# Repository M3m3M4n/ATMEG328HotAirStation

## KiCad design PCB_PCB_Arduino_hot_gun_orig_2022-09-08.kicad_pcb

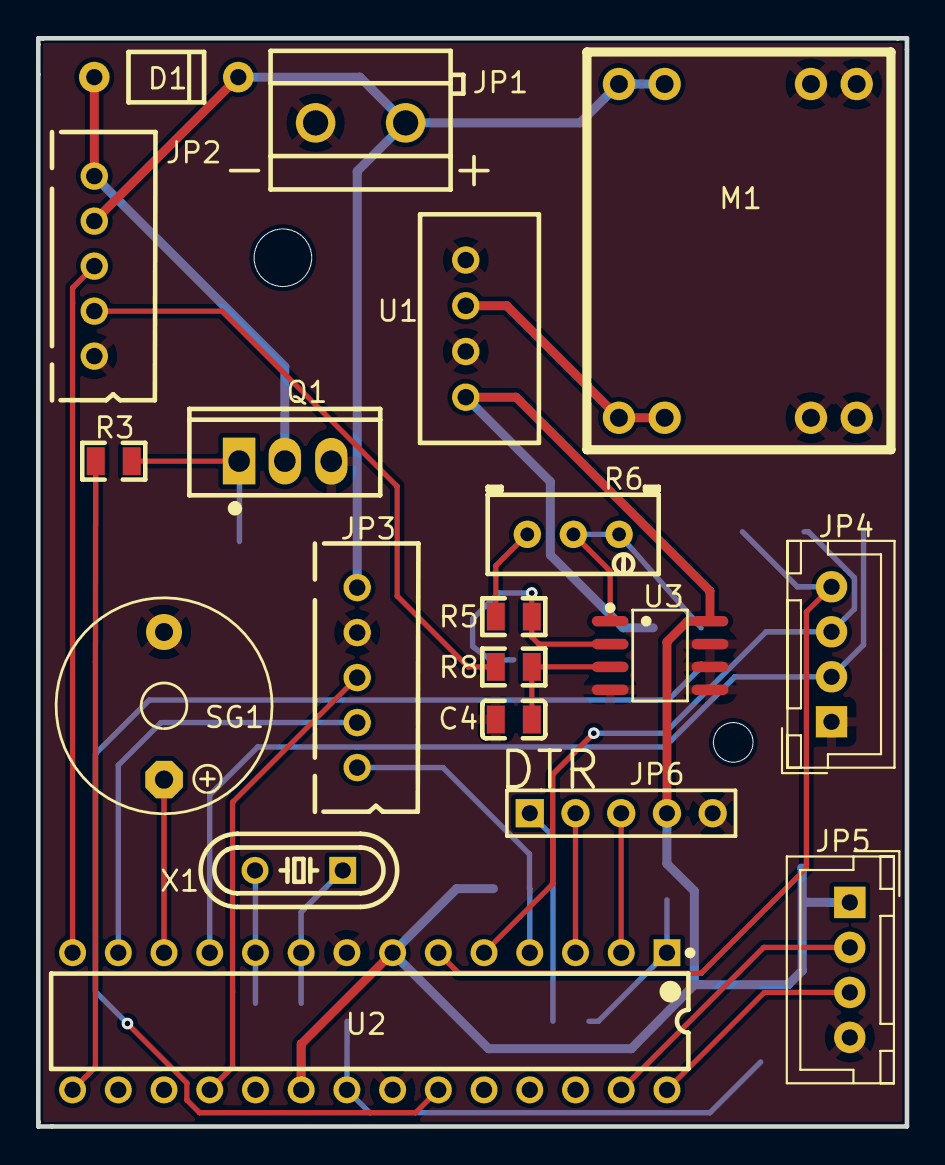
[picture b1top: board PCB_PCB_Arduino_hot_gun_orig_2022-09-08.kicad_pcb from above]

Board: 2 copper layers, 48.3 x 60.5 mm, 34 parts (0 on the bottom side), 30 nets.

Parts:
C1, C2: 22pF; C0805
C3, C4, C5, C6, C7, C8: 100n; C0805
C9, C10: 100u; C0805
D1: FR107; DO-41_BD2.8-L4.2-P8.00-D0.7-FD
JP1: 24v; CONN-TH_P5.00_KF301-5.0-2P
JP2: Air Gun; JST-XH-TH-5-2.5
JP3: INTERFACE; JST-XH-TH-5-2.5
JP4, JP5: REF; JST_XH_B04B-XH-A_04X2.50MM_STRAIGHT
JP6: UART; HDR-M-2.54_1X5
M1: .Designator; MP1584
Q1: IRFZ44NPBF; TO-220-3_L10.0-W4.5-P2.54-L
R1, R2, R5, R8, R11: 10k; R0805
R3: 100; R0805
R6: 500k; RES-ADJ_3296W
R7: 470; R0805
R9: 1k; R0805
SG1: BUZZER
U1: TME 0505S
U2: ATMEGA328P-PU; DIP-28_300MIL
U3: LM358; SOIC-8_L4.9-W3.9-P1.27-LS6.0-BL
U4: 1117-3.3; AMS_1117
X1: 16MHz; HC-49S

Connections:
24V: D1.2, JP1.2, JP2.4, JP3.5, M1.1, M1.2
+5V: C5.2, C9.2, JP5.1, JP6.4, R1.1, R11.1, U1.4, U2.7, U2.20, U3.8, U4.3
AC_RELAY: JP3.3, U2.18
AC_ZERO: JP3.1, R1.2, U2.4
BTN: C8.2, JP4.2, U2.11
D1_1: D1.1, JP2.5, Q1.2
ENC_L: C7.2, JP4.3, U2.5
ENC_R: C6.2, JP4.4, U2.6
FAN_POWER: R3.1, U2.15
GND: C1.2, C2.2, C4.1, C5.1, C6.1, C7.1, C8.1, C9.1, C10.1, JP1.1, JP2.1, JP3.4, JP4.1, JP5.4, JP6.5, M1.3, M1.4, M1.5, M1.6, Q1.3, R2.1, R9.1, U1.1, U1.3, U2.8, U2.22, U3.4, U3.5, U3.6, U3.7, U4.1
GUN_POWER: JP3.2, U2.13
GUN_REED: JP2.3, U2.14
GUN_TEMP: R7.1, U2.23
JP6_1: C3.2, JP6.1
R2_2: Q1.1, R2.2, R3.2
R5_1: R5.1, R6.3
R7_2: R6.1, R6.2, R7.2, U3.1
R8_1: C4.2, R8.1, U3.3
R8_2: JP2.2, R8.2
R9_2: R5.2, R9.2, U3.2
SCL: JP5.3, U2.28
SDA: JP5.2, U2.27
SG1_+: SG1.+, U2.12
U1_2: M1.7, M1.8, U1.2
U2_1: C3.1, R11.2, U2.1
U2_2: JP6.3, U2.2
U2_3: JP6.2, U2.3
U2_9: C1.1, U2.9, X1.1
U2_10: C2.1, U2.10, X1.2
U2_21: C10.2, U2.21, U4.2

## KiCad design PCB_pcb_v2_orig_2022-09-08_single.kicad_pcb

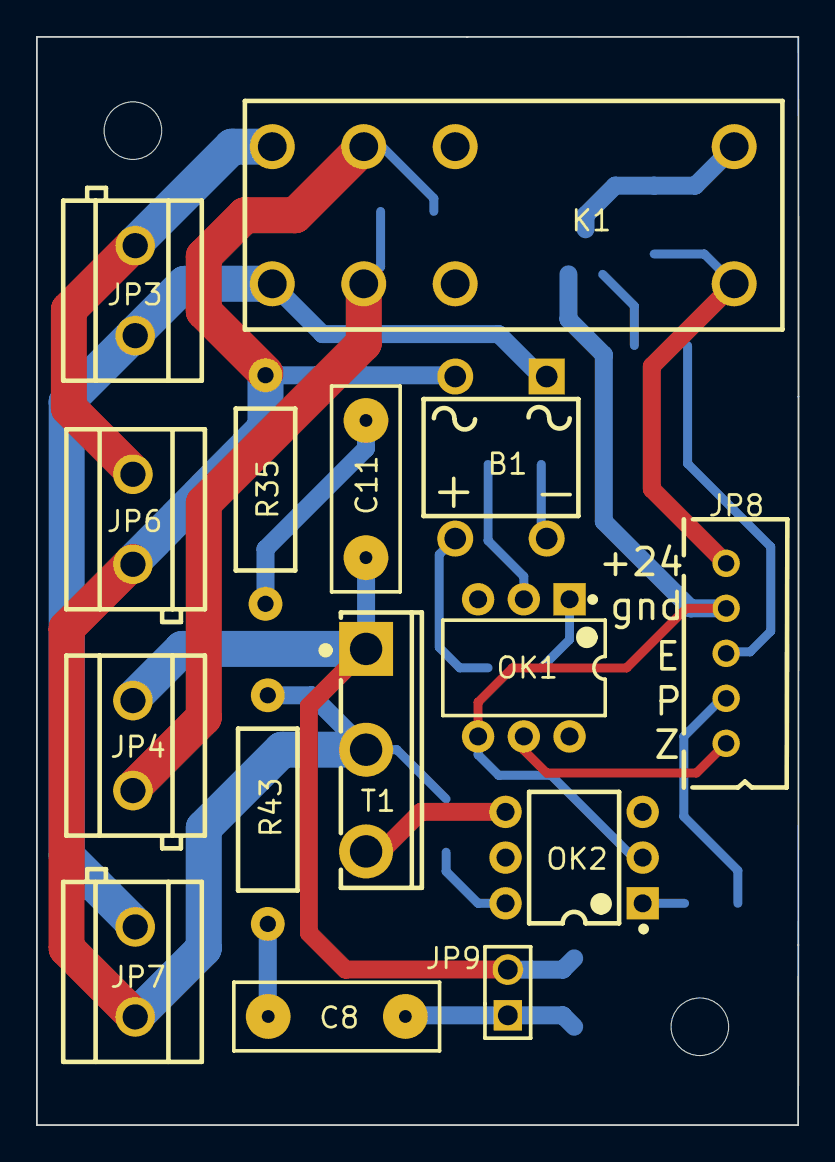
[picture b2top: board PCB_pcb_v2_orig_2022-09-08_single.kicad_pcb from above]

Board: 2 copper layers, 42.3 x 60.5 mm, 24 parts (0 on the bottom side), 22 nets.

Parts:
B1: -; DIO-BG-TH_DF
C8: 100nF; RAD-0.3
C11: 10nF; RAD-0.3
D3: 1N4001; SMAF_L3.5-W2.6-LS4.7-RD
D4: 1N4001F; SMAF_L3.5-W2.6-LS4.7-RD
JP3: 220v; CONN-TH_P5.00_KF301-5.0-2P
JP4: GUN; CONN-TH_P5.00_KF301-5.0-2P
JP6: Main Switch; CONN-TH_P5.00_KF301-5.0-2P
JP7: TO AC-DC 24v; CONN-TH_P5.00_KF301-5.0-2P
JP8: INTERFACE; JST-XH-TH-5-2.5
JP9: LED; HDR-M-2.54_1X2
K1: RTE24024; RELAY-HT14FD-SHG
OK1: 4N25M; DIP-6_L8.5-W6.4-P2.54-LS7.6-BL
OK2: MOC3052; DIP-6_L7.3-W6.5-P2.54-LS7.6-BL
R33, R34: 43k; R1206
R35: 39R; R_AXIAL-0.5
R36: 330; R1206
R37: 220; R1206
R42: 1k; R1206
R43: 1.8k; R_AXIAL-0.5
R44: 1M; R1206
T1: BTA41-600BRG; TOP3_L15.3-W4.5-P5.60-L
VT6: 2N2222; SOT-23-3_L2.9-W1.3-P1.90-LS2.4-TR

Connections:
+24V: D3.1, JP8.5, K1.1
AC1: JP3.2, JP6.1, K1.5
AC1_IN: B1.2, JP6.2, JP7.1, K1.6, R35.2, R36.1, R43.2, R44.2, T1.2
AC2: B1.1, JP3.1, JP7.2, K1.4
AC_ZERO: JP8.1, OK1.5
B1_3: B1.3, R33.1
B1_4: B1.4, R34.1
GND: JP8.4, OK1.4, OK2.2, VT6.1
GUN_POWER: JP8.2, R37.2
HOT_GUN_AC2: JP4.2, K1.3, R44.1
HOT_GUN_ENABLE: JP8.3, R42.2
JP9_1: C8.1, D4.2, JP9.1
K1_8: D3.2, K1.8, VT6.3
OK1_1: OK1.1, R33.2
OK1_2: OK1.2, R34.2
OK2_1: OK2.1, R37.1
OK2_6: OK2.6, R36.2
R35_1: C11.2, R35.1
R43_1: C8.2, R43.1
T1_1: C11.1, D4.1, JP4.1, JP9.2, T1.1
T1_3: OK2.4, T1.3
VT6_2: R42.1, VT6.2

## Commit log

2022-09-12 code
2022-09-13 script
2022-09-13 must find coord
2022-09-20 images
2022-09-21 change in lcd src
2022-09-22 note
2022-09-29 hotairpin
